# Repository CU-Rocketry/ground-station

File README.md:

# ground-station
Ground station for use with CUR SRAD flight computer with telemetry and user interface capabilities

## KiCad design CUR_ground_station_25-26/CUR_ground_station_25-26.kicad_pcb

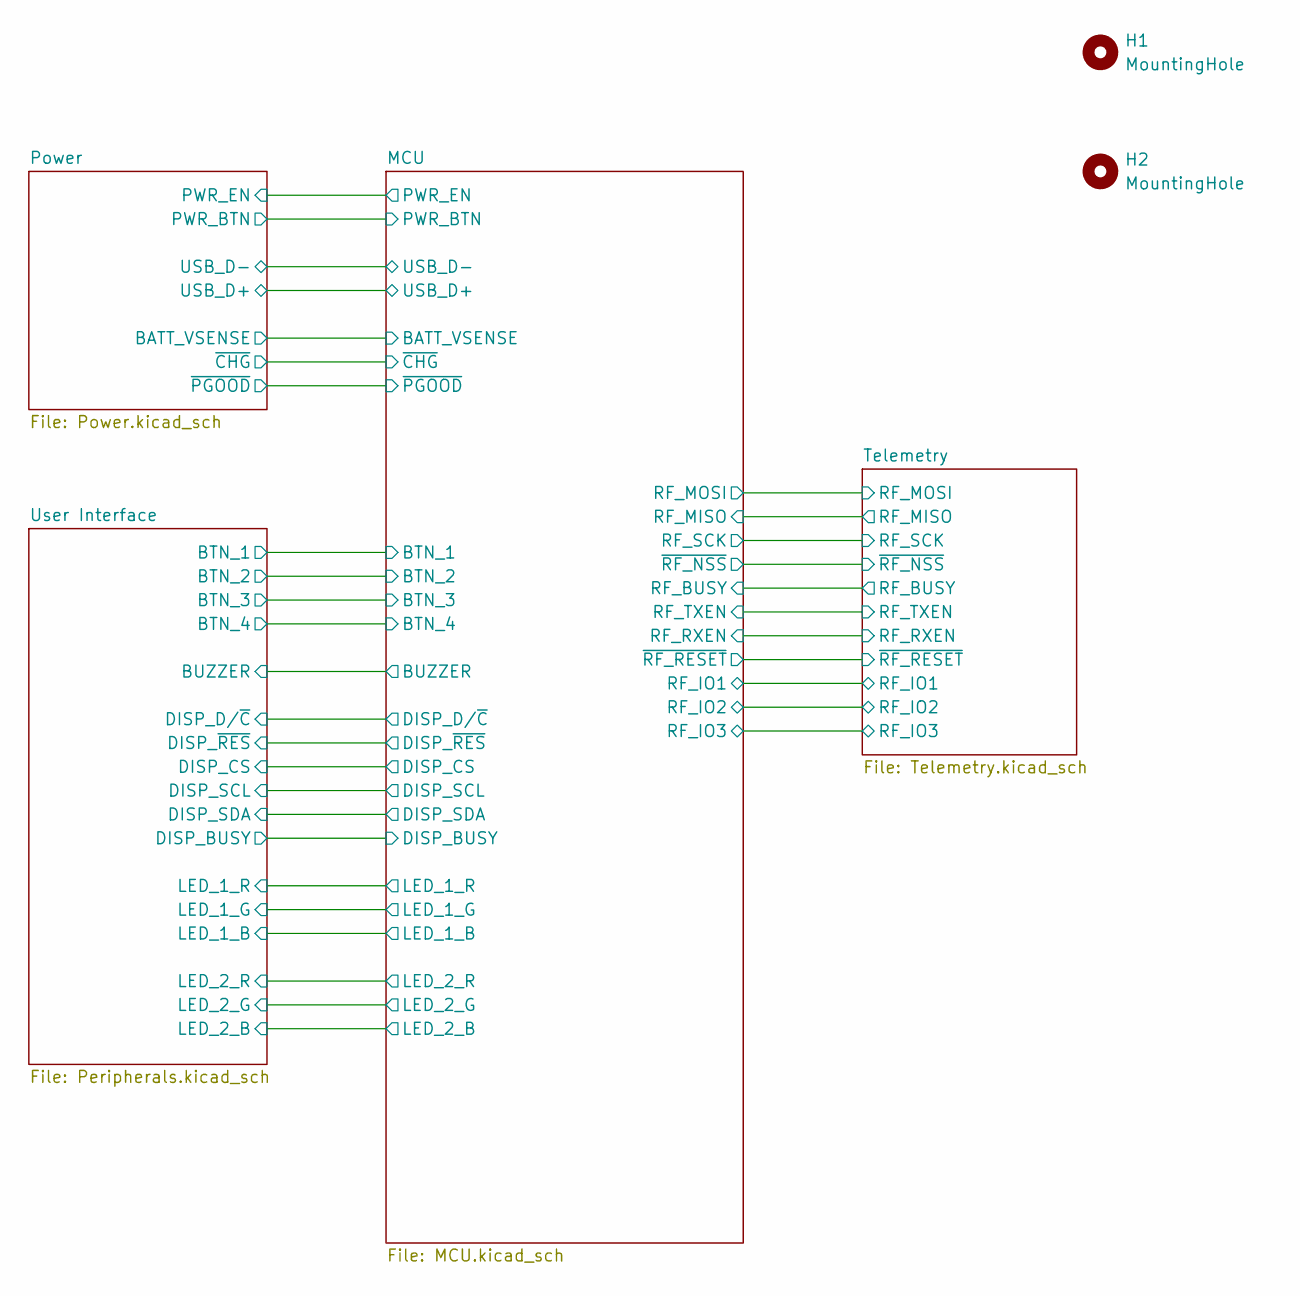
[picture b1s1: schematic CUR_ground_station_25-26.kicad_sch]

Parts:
H1, H2: MountingHole; MountingHole_3.2mm_M3

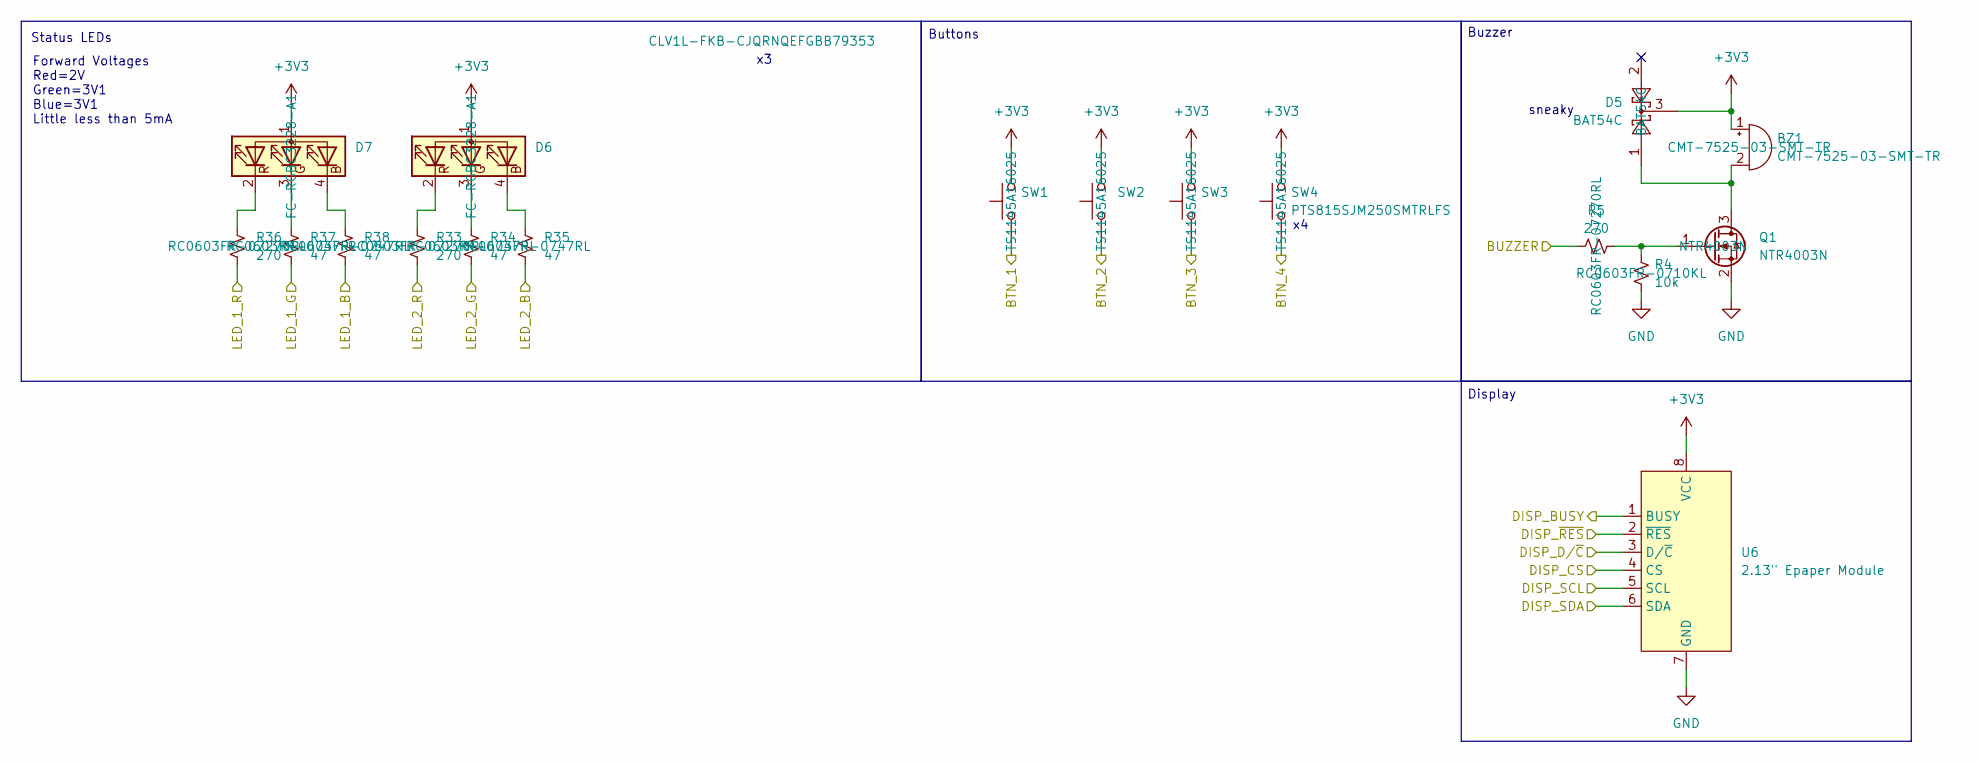
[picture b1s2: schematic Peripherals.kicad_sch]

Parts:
BZ1: CMT-7525-03-SMT-TR; XDCR_CMT-7525-03-SMT-TR; MPN CMT-7525-03-SMT-TR
D5: BAT54C; SOT-23; MPN BAT54C
D6, D7: CLV1L-FKB-CJQRNQEFGBB79353; LED_Cree-PLCC4_3.2x2.8mm_CCW; MPN FC-RGBC3228-A1
Q1: NTR4003N; SOT-23; MPN NTR4003N
R4: 10k; R_0603_1608Metric; MPN RC0603FR-0710KL
R5, R33, R36: 270; R_0603_1608Metric; MPN RC0603FR-07270RL
R34, R35, R37, R38: 47; R_0603_1608Metric; MPN RC0603FR-0747RL
SW1, SW2, SW3, SW4: PTS815SJM250SMTRLFS; SW_Push_PTS815_SJM_250_SMTR_LFS; MPN TS1145A16025
U6: 2.13" Epaper Module; WeAct-Studio-2.13-Epaper

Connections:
+3V3: BZ1.1 (+), D5.3, D6.1 (A), D7.1 (A), SW1.2, SW2.2, SW3.2, SW4.2, U6.8 (VCC); also elsewhere on the board
/MCU/BTN_1: SW1.1; also elsewhere on the board
/MCU/BTN_2: SW2.1; also elsewhere on the board
/MCU/BTN_3: SW3.1; also elsewhere on the board
/MCU/BTN_4: SW4.1; also elsewhere on the board
/MCU/BUZZER: R5.1; also elsewhere on the board
/MCU/DISP_BUSY: U6.1 (BUSY); also elsewhere on the board
/MCU/DISP_CS: U6.4 (CS); also elsewhere on the board
/MCU/DISP_D/~C: U6.3 (D/~C); also elsewhere on the board
/MCU/DISP_SCL: U6.5 (SCL); also elsewhere on the board
/MCU/DISP_SDA: U6.6 (SDA); also elsewhere on the board
/MCU/DISP_~RES: U6.2 (~RES); also elsewhere on the board
/MCU/LED_1_B: R38.2; also elsewhere on the board
/MCU/LED_1_G: R37.2; also elsewhere on the board
/MCU/LED_1_R: R36.2; also elsewhere on the board
/MCU/LED_2_B: R35.2; also elsewhere on the board
/MCU/LED_2_G: R34.2; also elsewhere on the board
/MCU/LED_2_R: R33.2; also elsewhere on the board
GND: Q1.2 (S), R4.2, U6.7 (GND); also elsewhere on the board
unnamed: BZ1.2 (-), D5.1, Q1.3 (D)
unnamed: D6.4 (BK), R35.1
unnamed: D6.3 (GK), R34.1
unnamed: D6.2 (RK), R33.1
unnamed: D7.4 (BK), R38.1
unnamed: D7.3 (GK), R37.1
unnamed: D7.2 (RK), R36.1
unnamed: Q1.1 (G), R4.1, R5.2

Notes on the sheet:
Forward Voltages Red=2V Green=3V1 Blue=3V1 Little less than 5mA
Buzzer
Buttons
sneaky
Display
Status LEDs

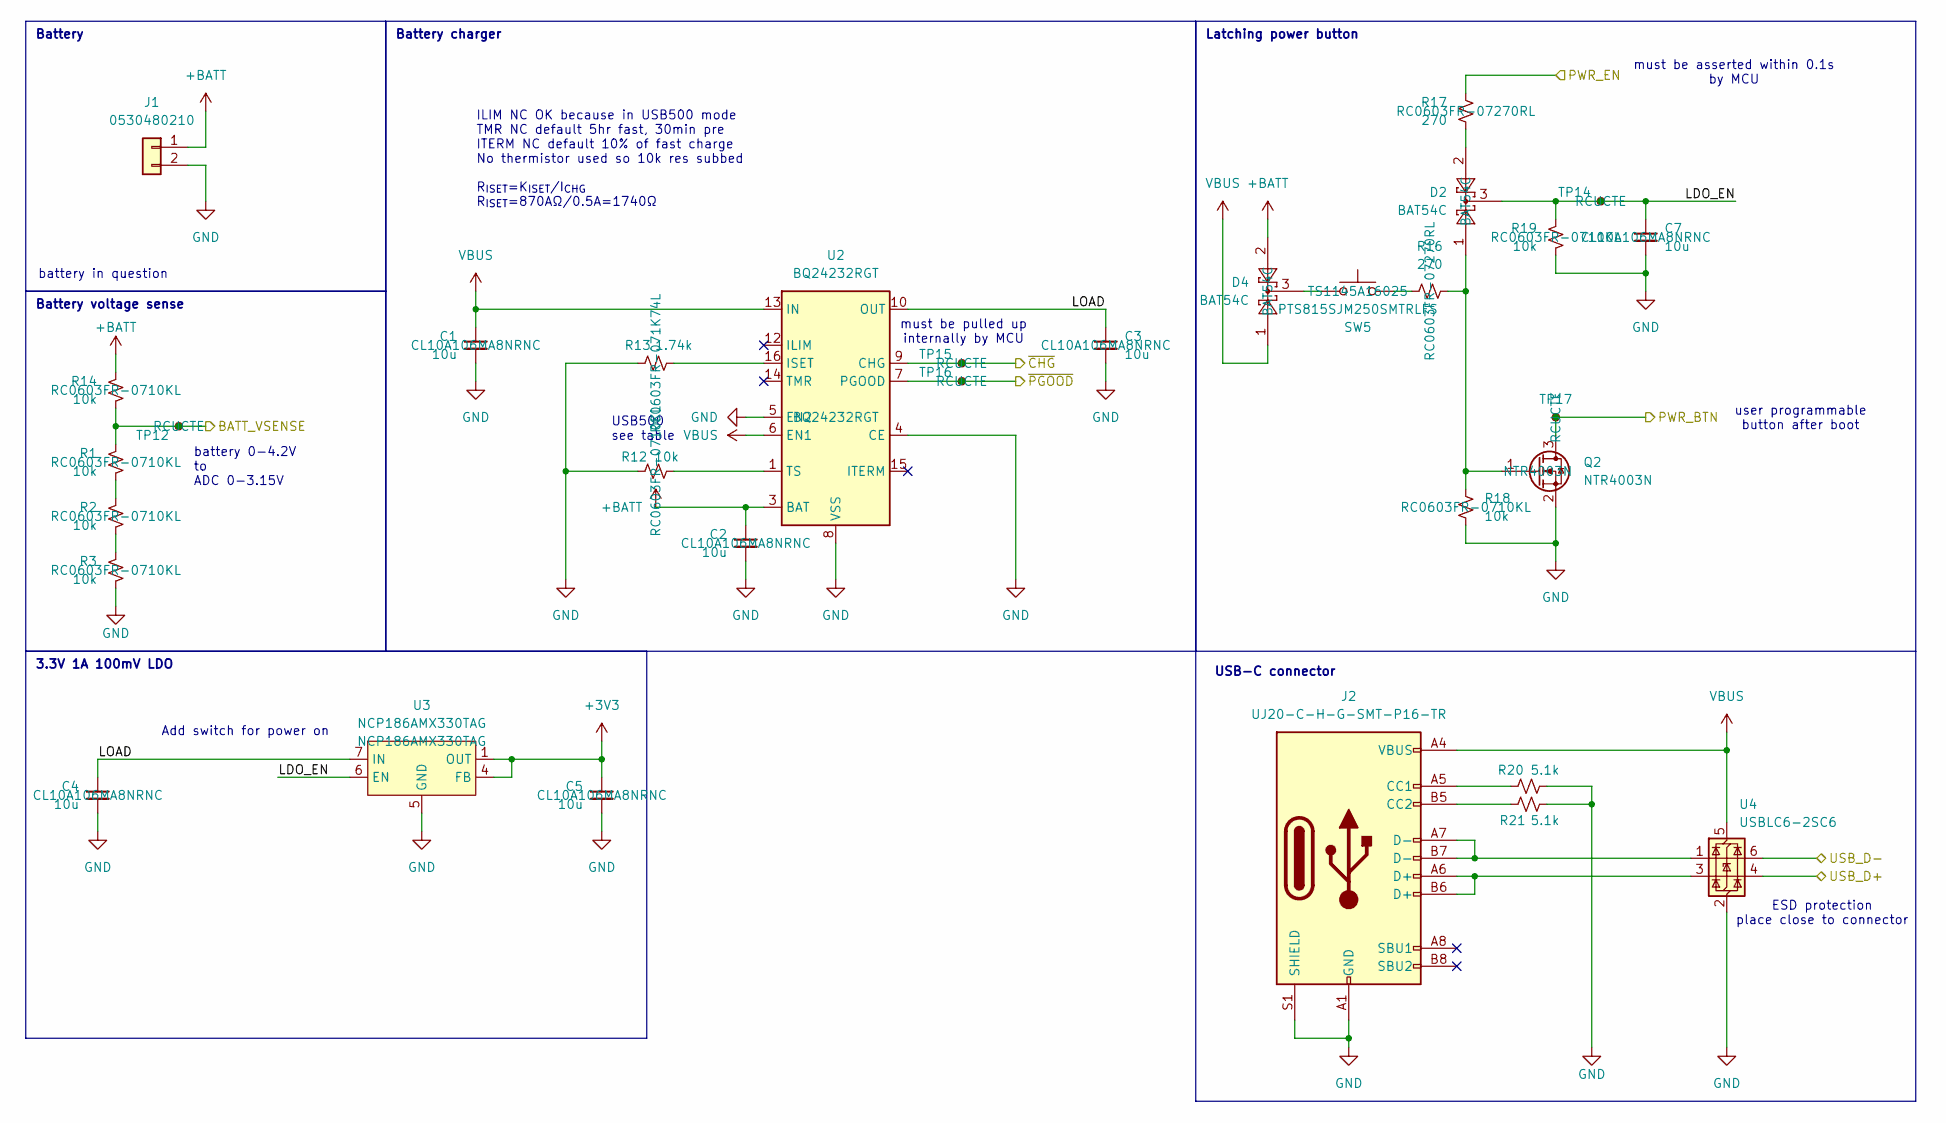
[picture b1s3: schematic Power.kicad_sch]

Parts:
C1, C2, C3, C4, C5, C7: 10u; C_0603_1608Metric; MPN CL10A106MA8NRNC
D2, D4: BAT54C; SOT-23; MPN BAT54C
J1: 0530480210; Molex_PicoBlade_53048-0210_1x02_P1.25mm_Horizontal; MPN 1.25-2AW
J2: UJ20-C-H-G-SMT-P16-TR; SAMESKY_UJ20-C-H-G-SMT-P16-TR; MPN UJ20-C-H-G-SMT-P16-TR
Q2: NTR4003N; SOT-23; MPN NTR4003N
R1, R2, R3, R12, R14, R18, R19: 10k; R_0603_1608Metric; MPN RC0603FR-0710KL
R13: 1.74k; R_0603_1608Metric; MPN RC0603FR-071K74L
R16, R17: 270; R_0603_1608Metric; MPN RC0603FR-07270RL
R20, R21: 5.1k; R_0603_1608Metric; MPN RC0603FR-075K1L
SW5: PTS815SJM250SMTRLFS; SW_Push_PTS815_SJM_250_SMTR_LFS; MPN TS1145A16025
TP12, TP14, TP15, TP16, TP17: TestPoint_Small; TestPoint_Chip_RCUCTE_0603; MPN RCUCTE
U2: BQ24232RGT; VQFN-16-1EP_3x3mm_P0.5mm_EP1.68x1.68mm; MPN BQ24232RGT
U3: NCP186AMX330TAG; NCP186_XDFN8_1.6x1.2mm_P0.4mm; MPN NCP186AMX330TAG
U4: USBLC6-2SC6; SOT-23-6; MPN USBLC6-2SC6

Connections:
+3V3: C5.1, U3.1 (OUT), U3.2 (OUT), U3.4 (FB); also elsewhere on the board
+BATT: C2.1, D4.2, J1.1, R14.1, U2.2 (BAT), U2.3 (BAT)
/MCU/BATT_VSENSE: R1.1, R14.2, TP12.1; also elsewhere on the board
/MCU/PWR_BTN: Q2.3 (D), TP17.1; also elsewhere on the board
/MCU/PWR_EN: R17.1; also elsewhere on the board
/MCU/USB_D+: U4.4 (I/O2); also elsewhere on the board
/MCU/USB_D-: U4.6 (I/O1); also elsewhere on the board
/MCU/~CHG: TP15.1, U2.9 (CHG); also elsewhere on the board
/MCU/~PGOOD: TP16.1, U2.7 (PGOOD); also elsewhere on the board
/Power/LDO_EN: C7.1, D2.3, R19.1, TP14.1, U3.6 (EN)
GND: C1.2, C2.2, C3.2, C4.2, C5.2, C7.2, J1.2, J2.A1 (GND), J2.A12 (GND), J2.B1 (GND), J2.B12 (GND), J2.S1 (SHIELD), Q2.2 (S), R3.2, R12.1, R13.1, R18.2, R19.2, R20.2, R21.2, U2.4 (CE), U2.5 (EN2), U2.8 (VSS), U2.17 (VSS), U3.3 (N/C), U3.5 (GND), U3.9 (EPAD), U4.2 (GND); also elsewhere on the board
IN: C3.1, C4.1, U2.10 (OUT), U2.11 (OUT), U3.7 (IN), U3.8 (IN)
unnamed: D2.2, R17.2
unnamed: D4.3, SW5.1
unnamed: J2.A5 (CC1), R20.1
unnamed: J2.B5 (CC2), R21.1
unnamed: J2.A6 (D+), J2.B6 (D+), U4.3 (I/O2)
unnamed: J2.A7 (D-), J2.B7 (D-), U4.1 (I/O1)
unnamed: D2.1, Q2.1 (G), R16.2, R18.1
unnamed: R1.2, R2.1
unnamed: R2.2, R3.1
unnamed: R16.1, SW5.2
unnamed: R13.2, U2.16 (ISET)
unnamed: R12.2, U2.1 (TS)
VBUS: C1.1, D4.1, J2.A4 (VBUS), J2.A9 (VBUS), J2.B4 (VBUS), J2.B9 (VBUS), U2.6 (EN1), U2.13 (IN), U4.5 (VBUS)

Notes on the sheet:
R_{ISET}=K_{ISET}/I_{CHG} R_{ISET}=870AΩ/0.5A=1740Ω
must be asserted within 0.1s by MCU
3.3V 1A 100mV LDO
Battery voltage sense
USB-C connector
ILIM NC OK because in USB500 mode TMR NC default 5hr fast, 30min pre ITERM NC default 10% of fast charge No thermistor used so 10k res subbed
Battery
USB500 see table
Latching power button
Add switch for power on
battery 0-4.2V to ADC 0-3.15V
Battery charger
ESD protection place close to connector
must be pulled up internally by MCU
user programmable button after boot
battery in question

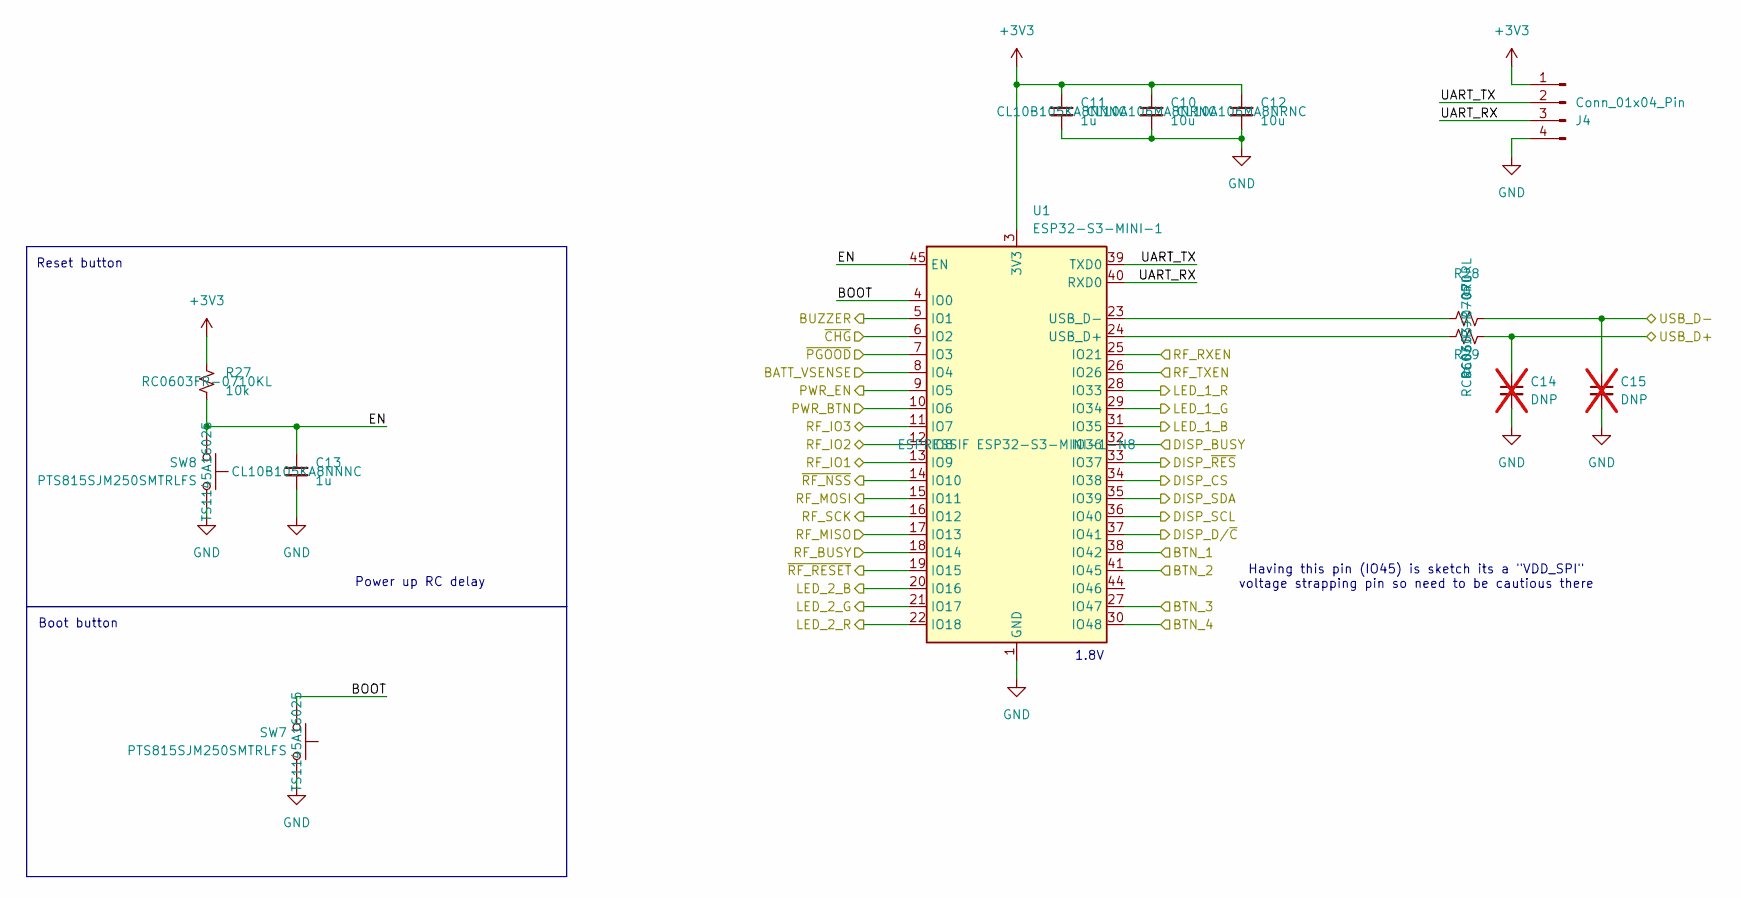
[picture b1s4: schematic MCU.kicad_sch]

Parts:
C10, C12: 10u; C_0603_1608Metric; MPN CL10A106MA8NRNC
C11, C13: 1u; C_0603_1608Metric; MPN CL10B105KA8NNNC
C14, C15: DNP; C_0603_1608Metric; not fitted
J4: Conn_01x04_Pin; PinHeader_1x04_P2.54mm_Vertical
R27: 10k; R_0603_1608Metric; MPN RC0603FR-0710KL
R28, R29: 0; R_0603_1608Metric; MPN RC0603JR-070RL
SW7, SW8: PTS815SJM250SMTRLFS; SW_Push_PTS815_SJM_250_SMTR_LFS; MPN TS1145A16025
U1: ESP32-S3-MINI-1; ESP32-S2-MINI-1; MPN ESPRESSIF ESP32-S3-MINI-1-N8

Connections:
+3V3: C10.1, C11.1, C12.1, J4.1, R27.1, U1.3 (3V3); also elsewhere on the board
/MCU/BATT_VSENSE: U1.8 (IO4); also elsewhere on the board
/MCU/BOOT: SW7.2, U1.4 (IO0)
/MCU/BTN_1: U1.38 (IO42); also elsewhere on the board
/MCU/BTN_2: U1.41 (IO45); also elsewhere on the board
/MCU/BTN_3: U1.27 (IO47); also elsewhere on the board
/MCU/BTN_4: U1.30 (IO48); also elsewhere on the board
/MCU/BUZZER: U1.5 (IO1); also elsewhere on the board
/MCU/DISP_BUSY: U1.32 (IO36); also elsewhere on the board
/MCU/DISP_CS: U1.34 (IO38); also elsewhere on the board
/MCU/DISP_D/~C: U1.37 (IO41); also elsewhere on the board
/MCU/DISP_SCL: U1.36 (IO40); also elsewhere on the board
/MCU/DISP_SDA: U1.35 (IO39); also elsewhere on the board
/MCU/DISP_~RES: U1.33 (IO37); also elsewhere on the board
/MCU/EN: C13.1, R27.2, SW8.2, U1.45 (EN)
/MCU/LED_1_B: U1.31 (IO35); also elsewhere on the board
/MCU/LED_1_G: U1.29 (IO34); also elsewhere on the board
/MCU/LED_1_R: U1.28 (IO33); also elsewhere on the board
/MCU/LED_2_B: U1.20 (IO16); also elsewhere on the board
/MCU/LED_2_G: U1.21 (IO17); also elsewhere on the board
/MCU/LED_2_R: U1.22 (IO18); also elsewhere on the board
/MCU/PWR_BTN: U1.10 (IO6); also elsewhere on the board
/MCU/PWR_EN: U1.9 (IO5); also elsewhere on the board
/MCU/RF_BUSY: U1.18 (IO14); also elsewhere on the board
/MCU/RF_IO1: U1.13 (IO9); also elsewhere on the board
/MCU/RF_IO2: U1.12 (IO8); also elsewhere on the board
/MCU/RF_IO3: U1.11 (IO7); also elsewhere on the board
/MCU/RF_MISO: U1.17 (IO13); also elsewhere on the board
/MCU/RF_MOSI: U1.15 (IO11); also elsewhere on the board
/MCU/RF_RXEN: U1.25 (IO21); also elsewhere on the board
/MCU/RF_SCK: U1.16 (IO12); also elsewhere on the board
/MCU/RF_TXEN: U1.26 (IO26); also elsewhere on the board
/MCU/UART_RX: J4.3, U1.40 (RXD0)
/MCU/UART_TX: J4.2, U1.39 (TXD0)
/MCU/USB_D+: C14.1, R29.2; also elsewhere on the board
/MCU/USB_D-: C15.1, R28.2; also elsewhere on the board
/MCU/~CHG: U1.6 (IO2); also elsewhere on the board
/MCU/~PGOOD: U1.7 (IO3); also elsewhere on the board
/MCU/~RF_NSS: U1.14 (IO10); also elsewhere on the board
/MCU/~RF_RESET: U1.19 (IO15); also elsewhere on the board
GND: C10.2, C11.2, C12.2, C13.2, C14.2, C15.2, J4.4, SW7.1, SW8.1, U1.1 (GND), U1.2 (GND), U1.42 (GND), U1.43 (GND), U1.46 (GND), U1.47 (GND), U1.48 (GND), U1.49 (GND), U1.50 (GND), U1.51 (GND), U1.52 (GND), U1.53 (GND), U1.54 (GND), U1.55 (GND), U1.56 (GND), U1.57 (GND), U1.58 (GND), U1.59 (GND), U1.60 (GND), U1.61 (GND), U1.62 (GND), U1.63 (GND), U1.64 (GND), U1.65 (GND); also elsewhere on the board
unnamed: R29.1, U1.24 (USB_D+)
unnamed: R28.1, U1.23 (USB_D-)

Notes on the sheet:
Boot button
1.8V
Power up RC delay
Reset button
Having this pin (IO45) is sketch its a "VDD_SPI" voltage strapping pin so need to be cautious there

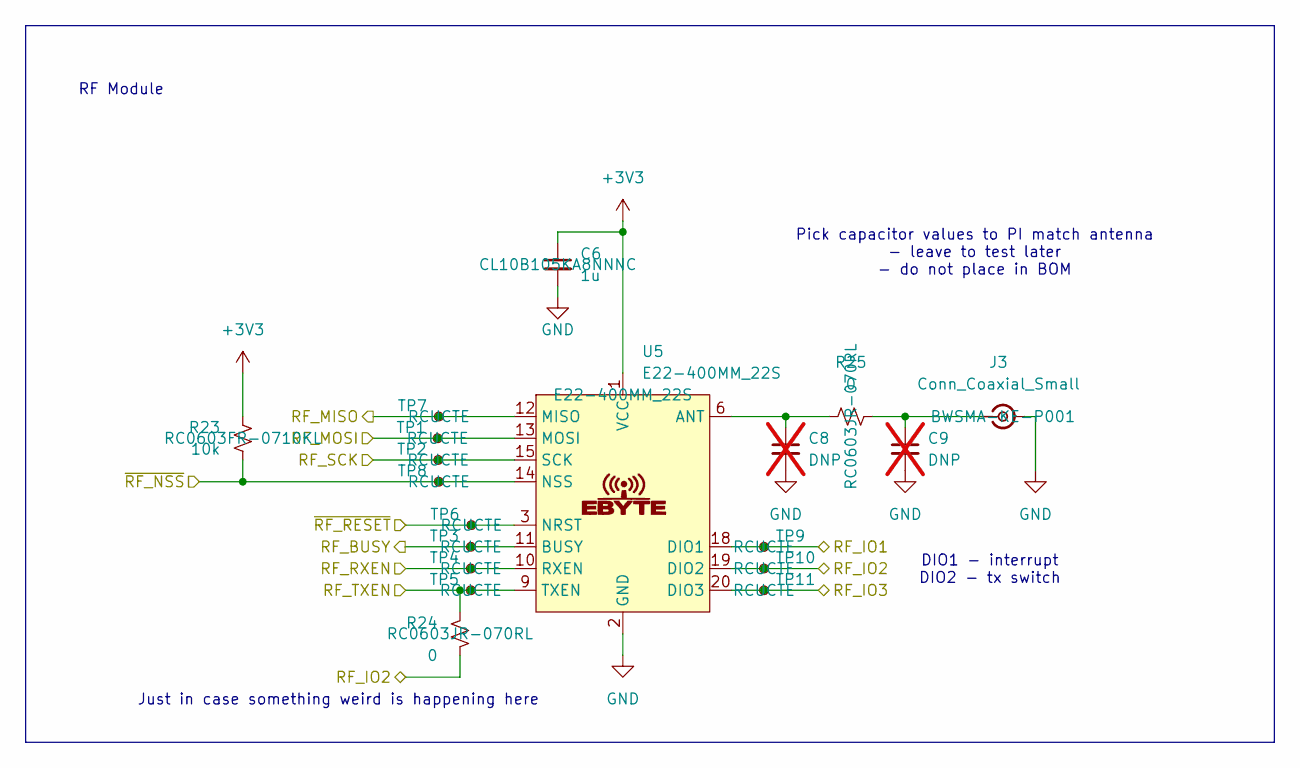
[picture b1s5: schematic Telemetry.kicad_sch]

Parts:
C6: 1u; C_0603_1608Metric; MPN CL10B105KA8NNNC
C8, C9: DNP; C_0603_1608Metric; not fitted
J3: Conn_Coaxial_Small; Conn_Coaxial_RFSOLUTIONS_CON-SMA-EDGE-S; MPN BWSMA-KE-P001
R23: 10k; R_0603_1608Metric; MPN RC0603FR-0710KL
R24, R25: 0; R_0603_1608Metric; MPN RC0603JR-070RL
TP1, TP2, TP3, TP4, TP5, TP6, TP7, TP8, TP9, TP10, TP11: TestPoint_Small; TestPoint_Chip_RCUCTE_0603; MPN RCUCTE
U5: E22-400MM_22S; EBYTE_LoRA_E22-400MM22S; MPN E22-400MM_22S

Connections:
+3V3: C6.1, R23.1, U5.1 (VCC); also elsewhere on the board
/MCU/RF_BUSY: TP3.1, U5.11 (BUSY); also elsewhere on the board
/MCU/RF_IO1: TP9.1, U5.18 (DIO1); also elsewhere on the board
/MCU/RF_IO2: R24.2, TP10.1, U5.19 (DIO2); also elsewhere on the board
/MCU/RF_IO3: TP11.1, U5.20 (DIO3); also elsewhere on the board
/MCU/RF_MISO: TP7.1, U5.12 (MISO); also elsewhere on the board
/MCU/RF_MOSI: TP1.1, U5.13 (MOSI); also elsewhere on the board
/MCU/RF_RXEN: TP4.1, U5.10 (RXEN); also elsewhere on the board
/MCU/RF_SCK: TP2.1, U5.15 (SCK); also elsewhere on the board
/MCU/RF_TXEN: R24.1, TP5.1, U5.9 (TXEN); also elsewhere on the board
/MCU/~RF_NSS: R23.2, TP8.1, U5.14 (NSS); also elsewhere on the board
/MCU/~RF_RESET: TP6.1, U5.3 (NRST); also elsewhere on the board
GND: C6.2, C8.2, C9.2, J3.2 (Ext), U5.2 (GND), U5.7 (GND), U5.16 (GND); also elsewhere on the board
unnamed: C9.1, J3.1 (In), R25.1
unnamed: C8.1, R25.2, U5.6 (ANT)

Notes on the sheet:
Pick capacitor values to PI match antenna - leave to test later - do not place in BOM
DIO1 - interrupt DIO2 - tx switch
RF Module
Just in case something weird is happening here

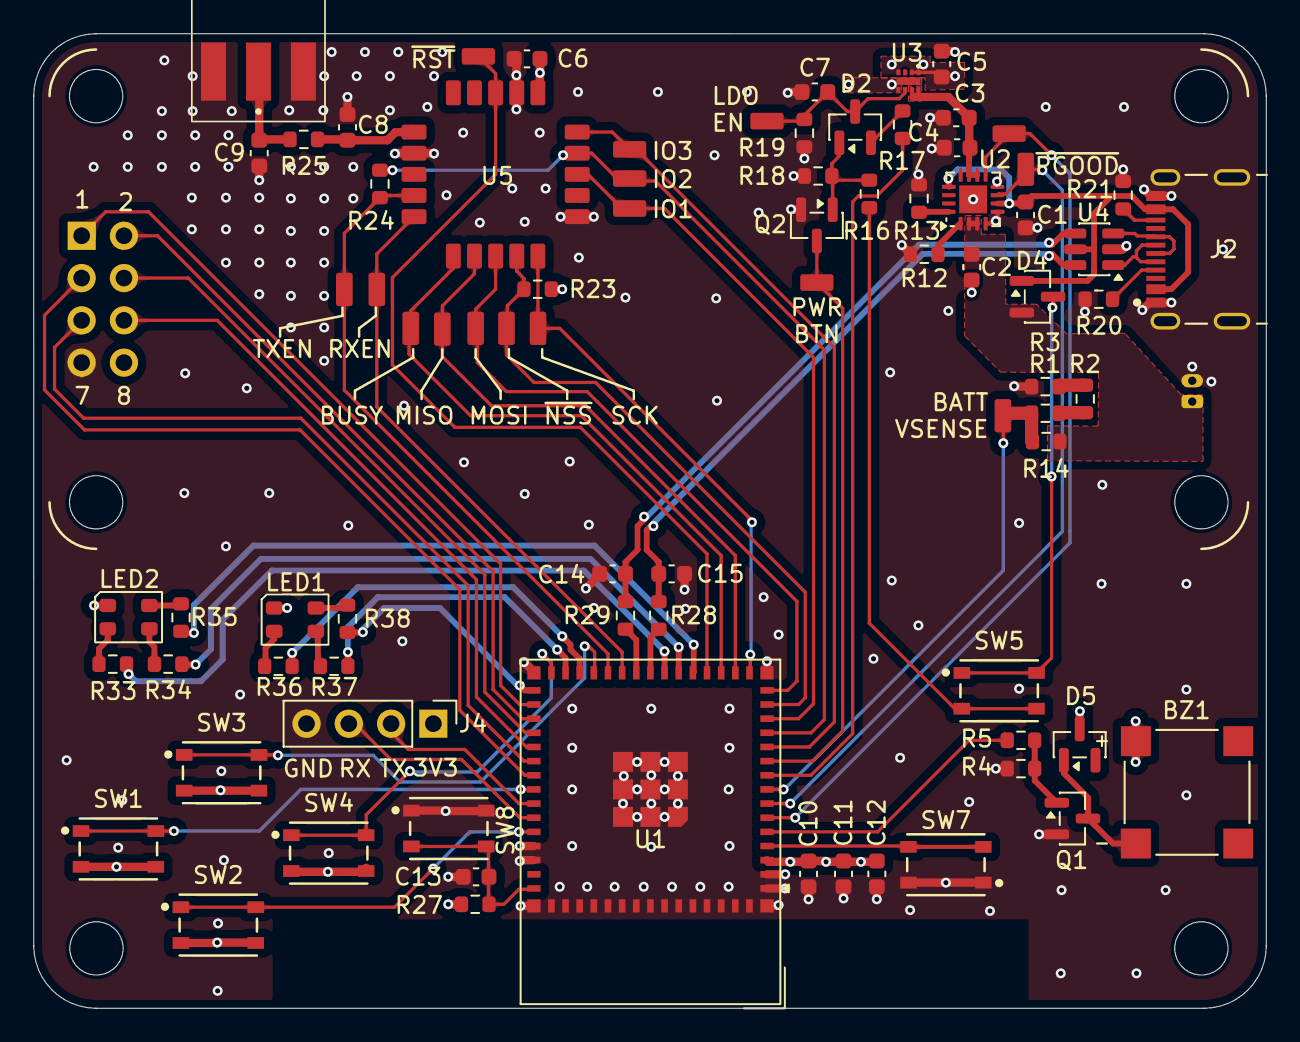
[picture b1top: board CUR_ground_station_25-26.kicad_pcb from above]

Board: 4 copper layers, 74.0 x 58.5 mm, 84 parts (1 on the bottom side), 69 nets.

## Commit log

2026-02-25 created kicad project file
2026-02-25 added sheets and mcu
2026-02-25 Add kicad-library submodule
2026-02-25 added power stuff
2026-02-25 sgAdded usbc to peripherals page
2026-02-25 sgAdded usbc to peripherals page but actually this time
2026-02-26 added user stuff
2026-02-26 Add footprints and symbols for power
2026-02-26 Implement battery management, soft power on, and LDO
2026-03-04 added buncha stuff from flight computer
2026-03-30 DNP the tuning capacitors on the RF trace
2026-03-30 Connect 3.3V and GND to MCU
2026-03-30 Correct soft power off circuit to support USB and battery
2026-03-30 Add epaper
2026-03-30 Cleanup UI sheet
2026-03-30 Cleanup peripherals again
2026-03-30 Add testpoints to power
2026-03-30 Add some required MCU components
2026-03-30 Sync sheet pins
2026-03-31 Started placing pins on MCU
2026-03-31 Change MCU, hookup more pins
2026-04-01 updating footprints
2026-04-01 added more footprints
2026-04-01 started layout-ing
2026-04-01 preliminary layout
2026-04-01 layout
2026-04-01 Power layout
2026-04-01 added power switch
2026-04-01 ignore the fact I added a switch
2026-04-01 started brief power routing
2026-04-03 found decent power layout
2026-04-03 more power layout ing
2026-04-06 BOM optimization
2026-04-06 Increase RC delay on power button
2026-04-06 Fix library issues in board update
2026-04-06 Update board shape, display, and USB C placement
2026-04-06 Fix USB capacitors
2026-04-06 Add mounting holes
2026-04-06 switched battery connector, put mounting holes in place
2026-04-07 Started routing power
2026-04-07 routing power section
2026-04-07 preliminary 3v3 rail routed
    routed on top layer. Its...interesting...
2026-04-08 changed to four layer board
2026-04-08 signal routing
2026-04-08 routing, ddrc addressed
2026-04-08 vias place, some labeling
2026-04-08 labing, adding gnd vias, other cleanup
2026-04-08 routing progress
2026-04-08 Add MPNs
2026-04-08 minor changes
2026-04-10 made gerbers, etc.
2026-04-10 Generate final gerbers
2026-04-10 gerber files zipped
2026-04-10 gerbers
2026-04-10 change gerbers
2026-04-10 gerbers again
2026-04-10 the RIGHT gerbers
2026-04-10 ger b e r
2026-04-10 Update gerbers after rotating battery connector
2026-04-10 Update kicad-library
2026-04-10 Update LDO and battery charger footprints
2026-04-10 Update gerbers
2026-04-10 Update fp-lib-table
2026-04-10 Update PCB (BAD we have to redo the TP labels)
2026-04-10 Find MPNs again
2026-04-10 Fix labels
2026-04-10 New gerbers
2026-04-16 New gerbers for nextpcb
